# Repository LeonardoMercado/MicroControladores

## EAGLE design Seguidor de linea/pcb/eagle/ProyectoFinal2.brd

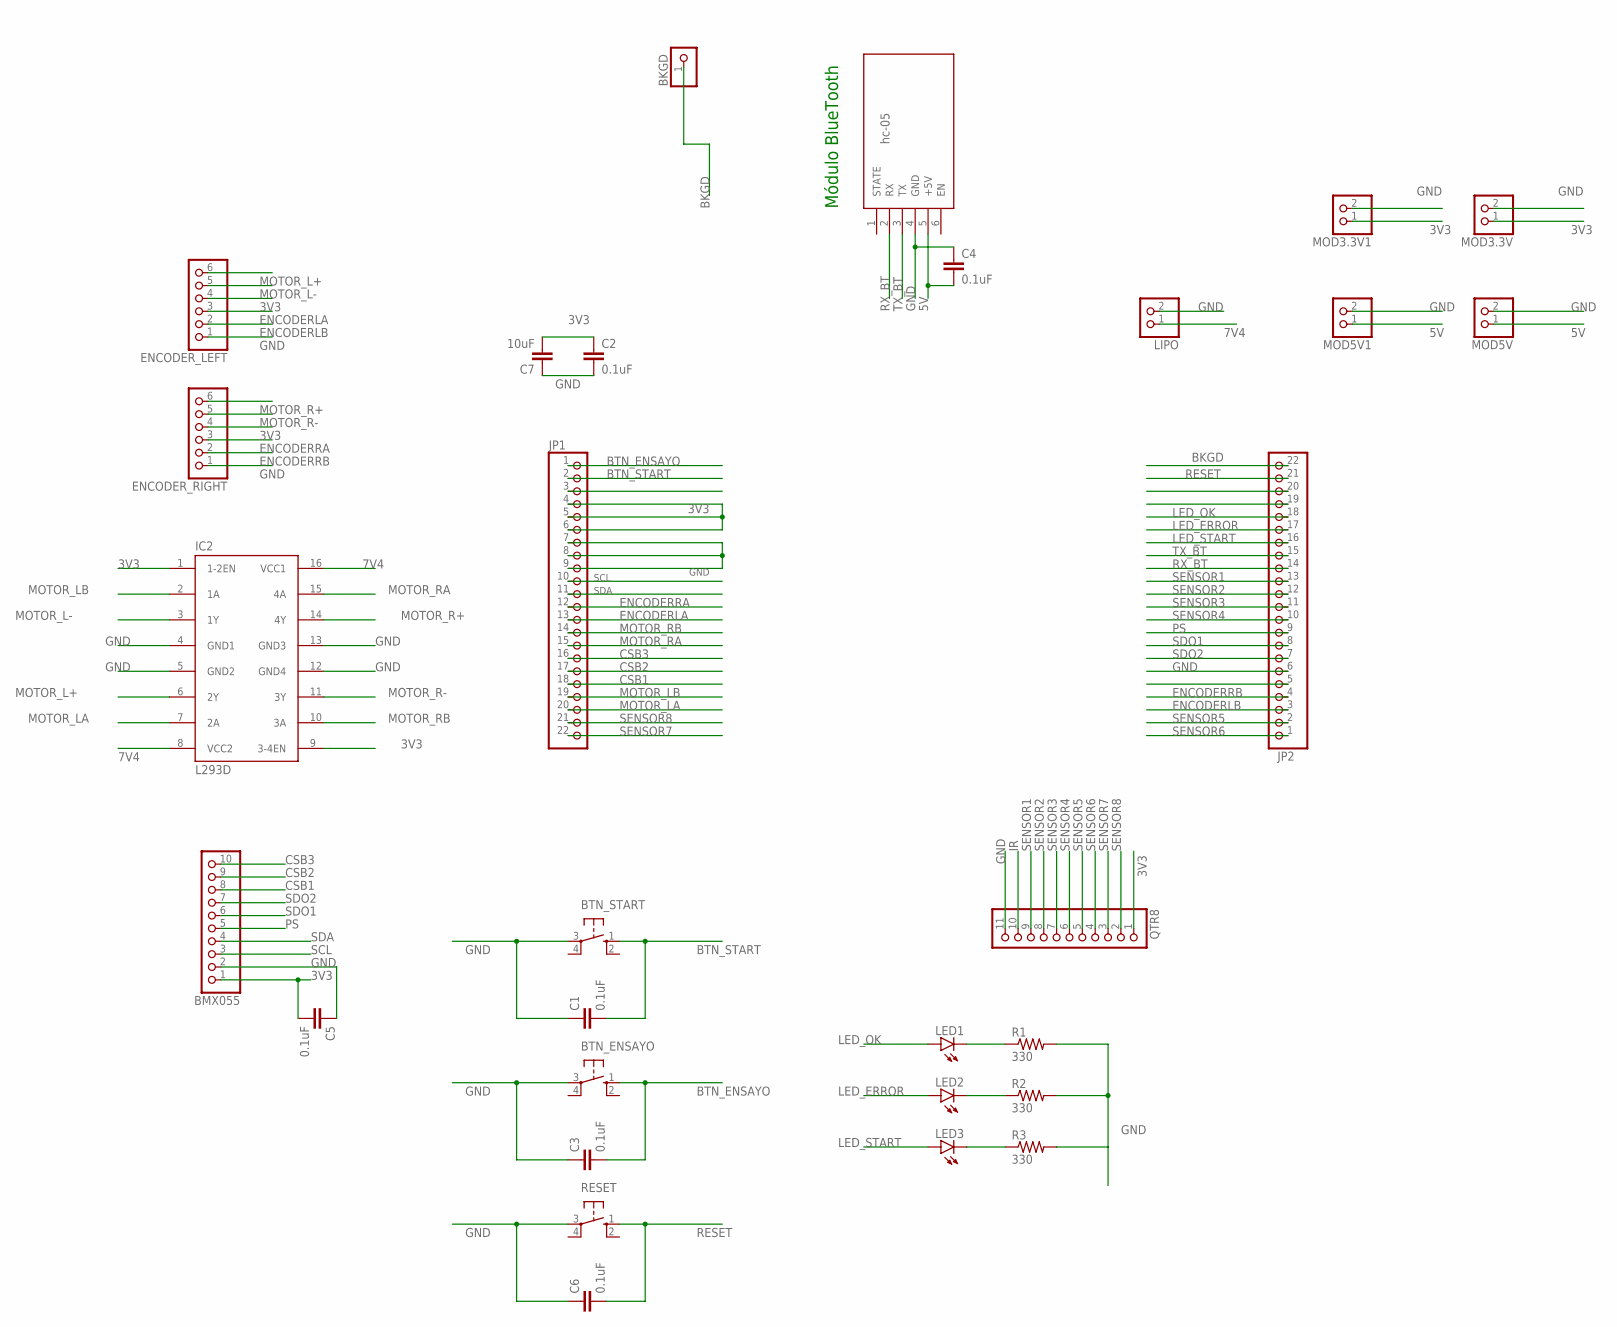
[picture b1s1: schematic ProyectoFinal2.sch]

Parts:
BKGD: PINHD-1X1; 1X01
BLUETOOTH: hc-05; WIRELESS-BLUETOOTH-HC-05
BMX055: PINHD-1X10; 1X10
BTN_ENSAYO: 10-XX; B3F-10XX
BTN_START: 10-XX; B3F-10XX
C1, C2, C3, C4, C5, C6: 0.1uF; C0805K
C7: 10uF; C1206K
ENCODER_LEFT: PINHD-1X6; 1X06
ENCODER_RIGHT: PINHD-1X6; 1X06
IC2: L293D; DIL16
JP1, JP2: PINHD-1X22; 1X22
LED1, LED2, LED3: LED5MM
LIPO: PINHD-1X2; 1X02
MOD3.3V, MOD3.3V1, MOD5V, MOD5V1: PINHD-1X2; 1X02
QTR8: PINHD-1X11; 1X11
R1, R2, R3: 330; R0805
RESET: 10-XX; B3F-10XX

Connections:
3V3: BMX055.1, C2.1, C5.2, C7.2, ENCODER_LEFT.4, ENCODER_RIGHT.4, IC2.1 (1-2EN), IC2.9 (3-4EN), JP1.4, JP1.5, JP1.6, MOD3.3V.1, MOD3.3V1.1, QTR8.1
5V: BLUETOOTH.5 (+5V), C4.2, MOD5V.1, MOD5V1.1
7V4: IC2.8 (VCC2), IC2.16 (VCC1), LIPO.1
BKGD: BKGD.1, JP2.22
BTN_ENSAYO: BTN_ENSAYO.1 (S), C3.2, JP1.1
BTN_START: BTN_START.1 (S), C1.2, JP1.2
CSB1: BMX055.8, JP1.18
CSB2: BMX055.9, JP1.17
CSB3: BMX055.10, JP1.16
ENCODERLA: ENCODER_LEFT.3, JP1.13
ENCODERLB: ENCODER_LEFT.2, JP2.3
ENCODERRA: ENCODER_RIGHT.3, JP1.12
ENCODERRB: ENCODER_RIGHT.2, JP2.4
GND: BLUETOOTH.4 (GND), BMX055.2, BTN_ENSAYO.3, BTN_START.3, C1.1, C2.2, C3.1, C4.1, C5.1, C6.1, C7.1, ENCODER_LEFT.1, ENCODER_RIGHT.1, IC2.4 (GND1), IC2.5 (GND2), IC2.12 (GND4), IC2.13 (GND3), JP1.7, JP1.8, JP1.9, JP2.6, LIPO.2, MOD3.3V.2, MOD3.3V1.2, MOD5V.2, MOD5V1.2, QTR8.11, R1.2, R2.2, R3.2, RESET.3
IR: QTR8.10
LED_ERROR: JP2.17, LED2.A
LED_OK: JP2.18, LED1.A
LED_START: JP2.16, LED3.A
MOTOR_L+: ENCODER_LEFT.6, IC2.6 (2Y)
MOTOR_L-: ENCODER_LEFT.5, IC2.3 (1Y)
MOTOR_LA: IC2.7 (2A), JP1.20
MOTOR_LB: IC2.2 (1A), JP1.19
MOTOR_R+: ENCODER_RIGHT.6, IC2.14 (4Y)
MOTOR_R-: ENCODER_RIGHT.5, IC2.11 (3Y)
MOTOR_RA: IC2.15 (4A), JP1.15
MOTOR_RB: IC2.10 (3A), JP1.14
unnamed: LED1.K (C), R1.1
unnamed: LED2.K (C), R2.1
unnamed: LED3.K (C), R3.1
PS: BMX055.5, JP2.9
RESET: C6.2, JP2.21, RESET.1 (S)
RX_BT: BLUETOOTH.2 (RX), JP2.14
SCL: BMX055.3, JP1.10
SDA: BMX055.4, JP1.11
SDO1: BMX055.6, JP2.8
SDO2: BMX055.7, JP2.7
SENSOR1: JP2.13, QTR8.9
SENSOR2: JP2.12, QTR8.8
SENSOR3: JP2.11, QTR8.7
SENSOR4: JP2.10, QTR8.6
SENSOR5: JP2.2, QTR8.5
SENSOR6: JP2.1, QTR8.4
SENSOR7: JP1.22, QTR8.3
SENSOR8: JP1.21, QTR8.2
TX_BT: BLUETOOTH.3 (TX), JP2.15

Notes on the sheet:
Módulo BlueTooth

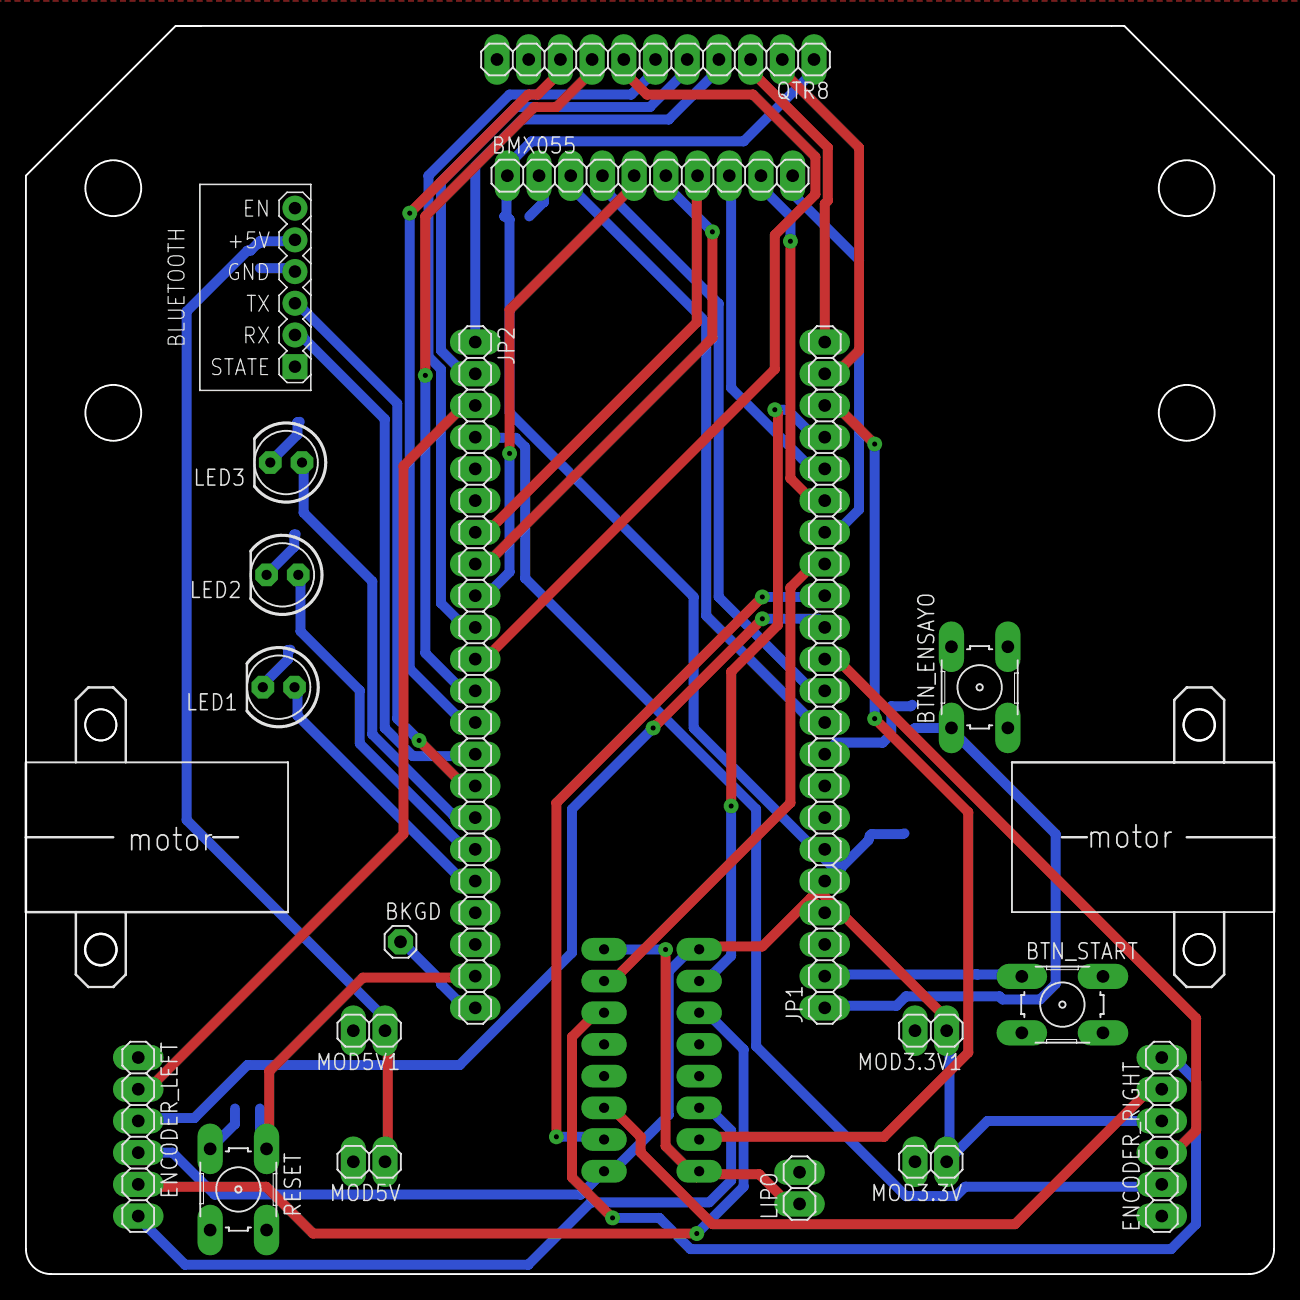
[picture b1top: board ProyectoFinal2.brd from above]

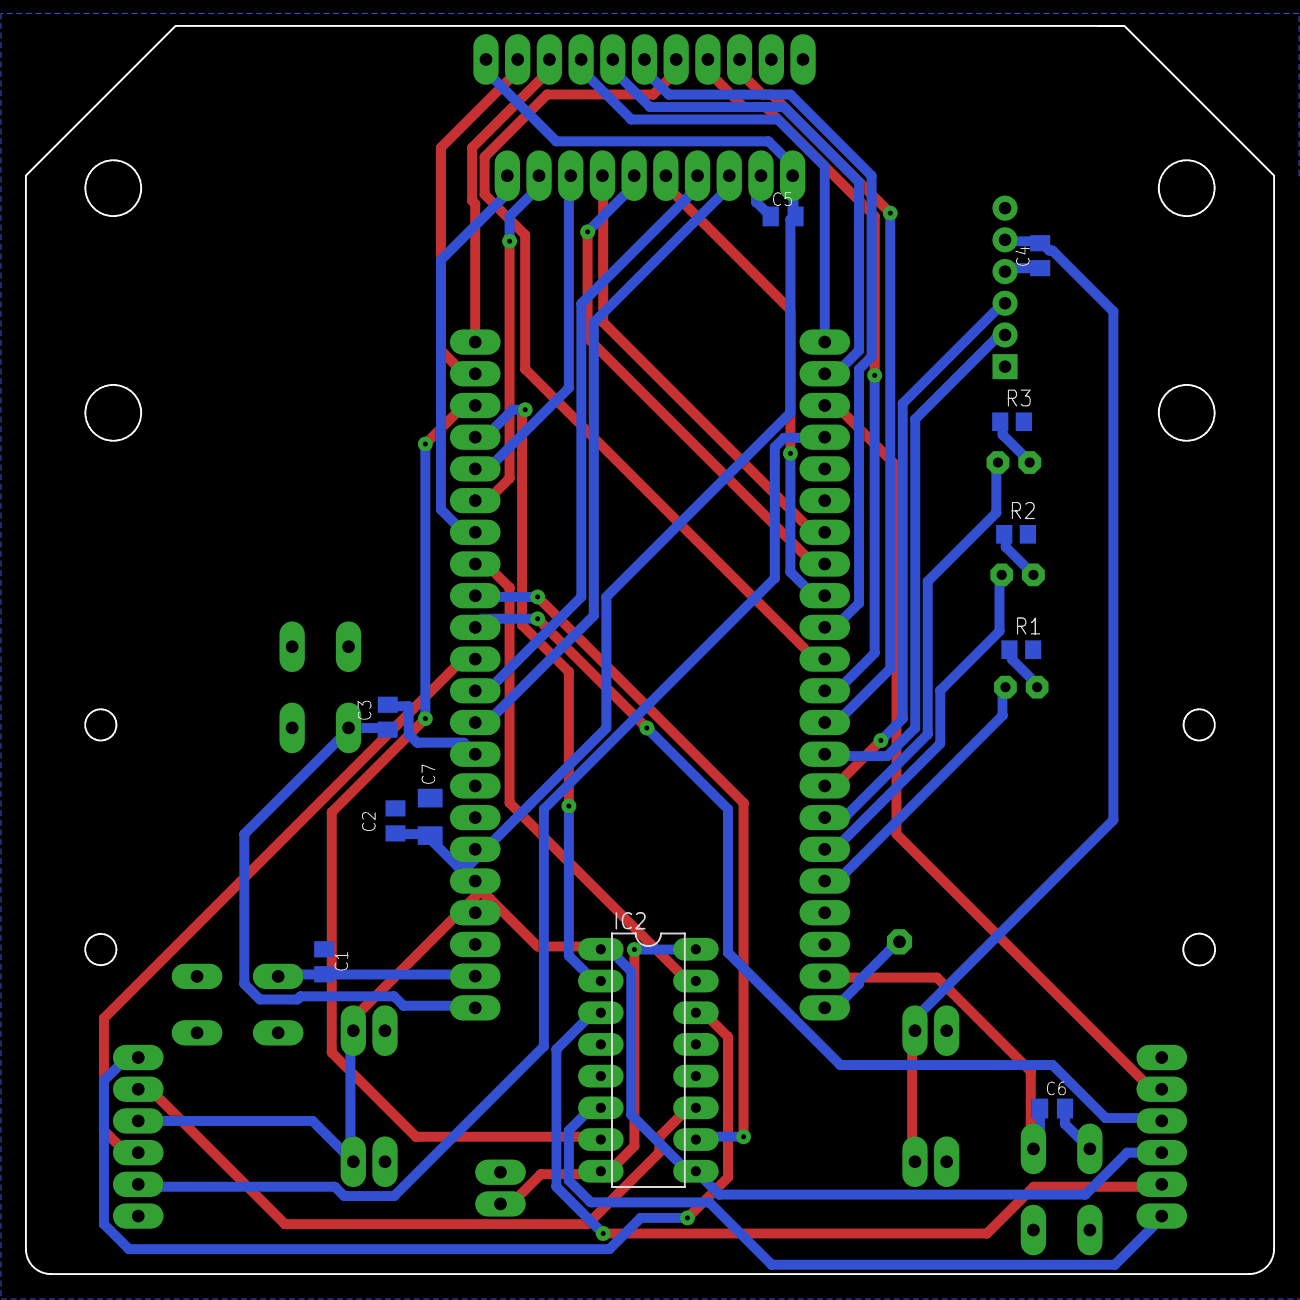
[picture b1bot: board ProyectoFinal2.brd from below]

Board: 2 copper layers, 100.0 x 100.0 mm, 30 parts (11 on the bottom side), 44 nets.

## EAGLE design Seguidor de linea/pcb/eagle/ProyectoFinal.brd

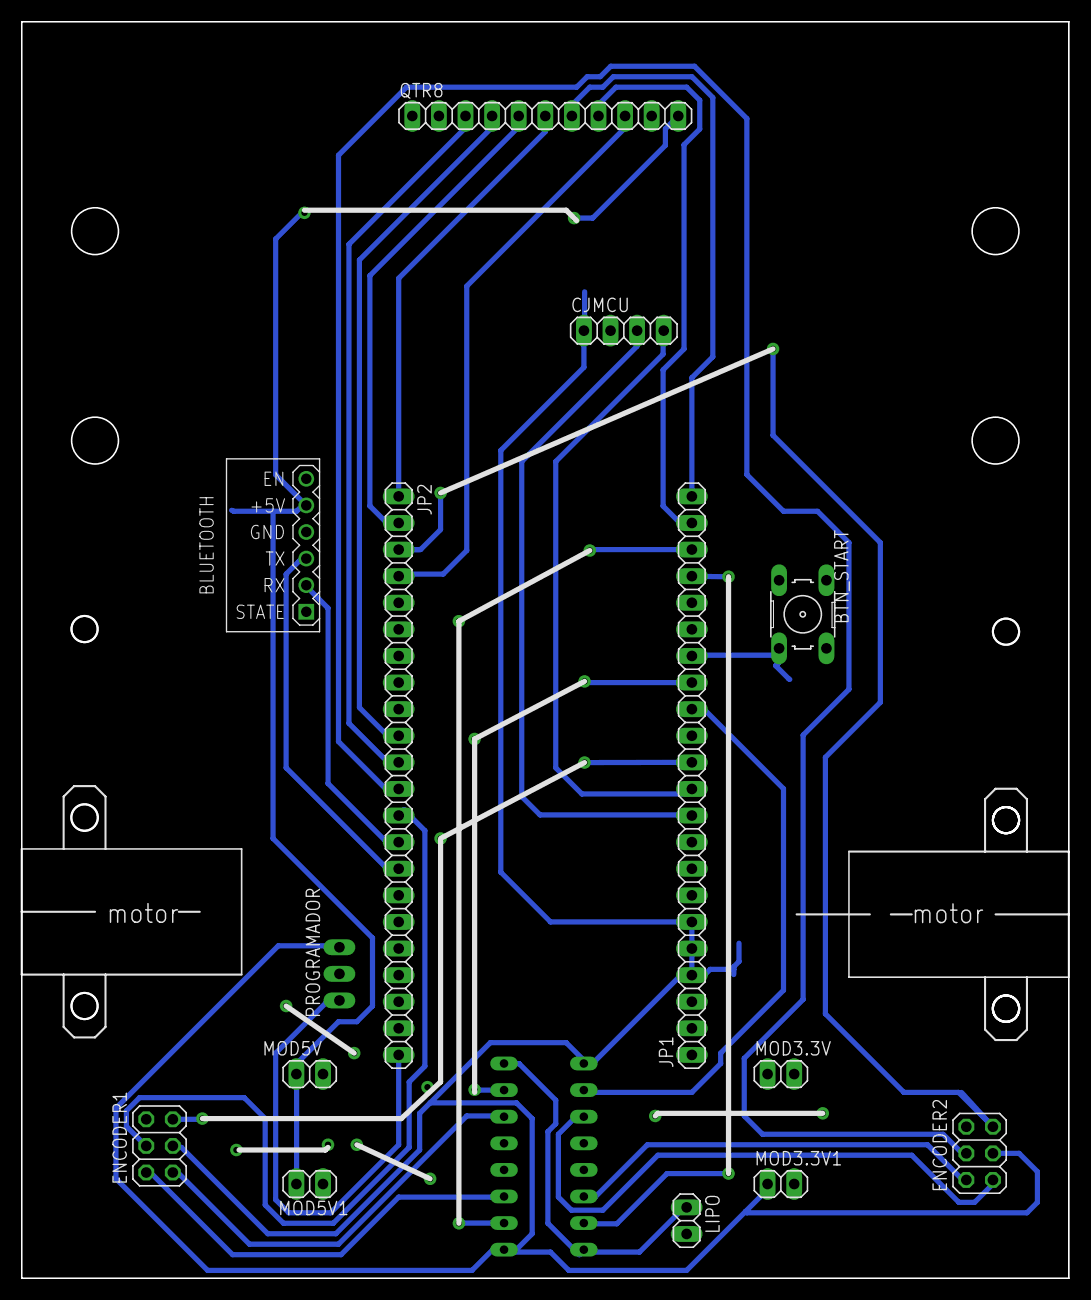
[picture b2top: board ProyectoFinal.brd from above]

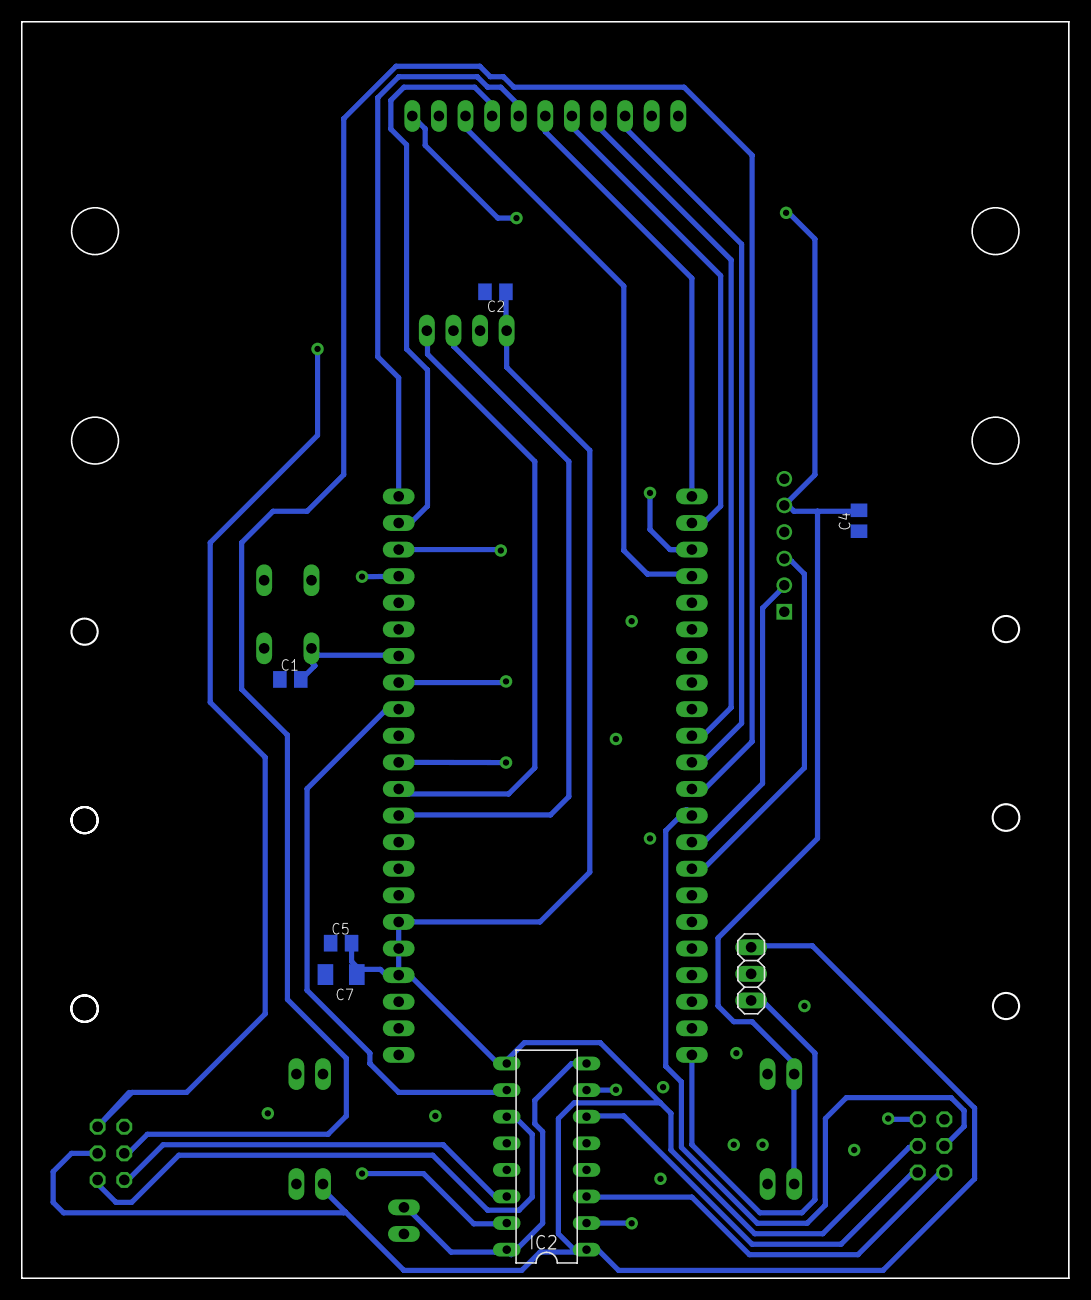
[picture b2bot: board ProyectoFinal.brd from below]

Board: 2 copper layers, 100.0 x 120.0 mm, 20 parts (7 on the bottom side), 29 nets.

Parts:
BLUETOOTH: hc-05; WIRELESS-BLUETOOTH-HC-05
BTN_START: B3F-10XX
C1, C2, C4, C5: 0.1uF; C0805K
C7: 10uF; C1206K
CJMCU: 1X04
ENCODER1, ENCODER2: 2X03
IC2: L293D; DIL16
JP1, JP2: 1X22
LIPO: 1X02
MOD3.3V, MOD3.3V1, MOD5V, MOD5V1: 1X02
PROGRAMADOR: 1X03
QTR8: 1X11

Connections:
3V3: C2.1, C5.2, C7.2, CJMCU.1, ENCODER1.3, ENCODER2.3, IC2.1, IC2.9, JP1.4, JP1.5, JP1.6, MOD3.3V1.1, PROGRAMADOR.3
5V: BLUETOOTH.5, C4.2, MOD5V.1, MOD5V1.1
7V4: IC2.8, IC2.16, LIPO.1
ADC2: JP2.11, QTR8.3
ADC3: JP2.10, QTR8.4
ADC4: JP2.2, QTR8.5
ADC5: JP2.1, QTR8.6
ADC6: JP1.22, QTR8.7
ADC7: JP1.21, QTR8.8
ADC8: JP2.4, QTR8.9
BKGD: JP2.22, PROGRAMADOR.1
BTN_START: BTN_START.1, C1.2, JP1.16
ENCODER1_1: ENCODER1.4, JP2.13
ENCODER1_2: ENCODER1.5, JP1.12
ENCODER2_1: ENCODER2.4, JP2.12
ENCODER2_2: ENCODER2.5, JP2.3
GND: BLUETOOTH.4, BTN_START.3, C1.1, C2.2, C4.1, C5.1, C7.1, CJMCU.2, ENCODER1.6, ENCODER2.6, IC2.4, IC2.5, IC2.12, IC2.13, JP1.7, JP1.8, JP1.9, JP2.6, LIPO.2, MOD3.3V.2, MOD3.3V1.2, MOD5V.2, MOD5V1.2, PROGRAMADOR.2, QTR8.1
MOTOR1_IN1: IC2.2, JP1.20
MOTOR1_IN2: IC2.7, JP1.15
MOTOR1_OUT1: ENCODER1.1, IC2.6
MOTOR1_OUT2: ENCODER1.2, IC2.3
MOTOR2_IN1: IC2.15, JP1.19
MOTOR2_IN2: IC2.10, JP1.14
MOTOR2_OUT1: ENCODER2.1, IC2.11
MOTOR2_OUT2: ENCODER2.2, IC2.14
RX_BT: BLUETOOTH.2, JP2.14
SCL: CJMCU.3, JP1.10
SDA: CJMCU.4, JP1.11
TX_BT: BLUETOOTH.3, JP2.15

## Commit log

2019-04-13 v1.0
    Se implementa el código enviado al correo
2019-04-13 v1.1
    Se modifico el puerto de entrada del push button y el puerto de salida del led
2019-04-16 V1.0
    Se implementa el código enviado, se analiza linea a linea y se comenta su acción
2019-04-23 vs 1.0
    Se implementa el código para encender 1 led y se modifican los puertos de entrada y de salida.
2019-04-23 v1.1
    Se realizan cambios en las etiquetas a implementar.
2019-04-24 Create freqLedRGB.asm
    Encendido led RGB cada 2.5s
2019-04-24 v1.2
    Se implementa el antirebote por SW y las especificaciones de los OpCode y los modos de direcionamiento
2019-05-03 v1.3
    Se implementa el Debugger de la etiqueta antirrebote.
2019-05-08 Ajuste leds y RTI lab4
2019-05-08 Código de retardos funcionando
2019-05-08 Direccionamiento indexado sin offset
2019-05-14 Código toggle_led T=4s
2019-05-14 Incluye vector interrupción MITM
2019-05-14 Código comentado
2019-05-21 Revert "V2"
    This reverts commit e91b2cf7e1e8bfc91f57d2a8d6e4e909c6e53531, reversing
    changes made to 079b767442dc883627aac7999d236b1ab7ce7748.
2019-05-21 Revert "Revert "V2""
    This reverts commit bc979bf9f36cf7630d5f124ff7b2e6652c294545.
2019-05-27 ajuste interrupción RTC
2019-05-28 v1.0
    Se carga el avanze del Laboratorio 7
2019-05-29 v1.1
    Se realizan mejoras y rotulados necesarios.
2019-05-29 V 1.1
2019-05-30 V.1.0
    Código ej Sebastian baud rate 19200 sin paridad FUNCIONANDO
2019-05-31 v1.0
    blalgl
2019-05-31 V1.0
2019-05-31 Reciclado del Lab6
    Reciclado, hay que hacerle algunas modificaciones
2019-05-31 Reciclado Lab6
    Actualizado: Display muestra un dato numerico, enciende el led RGB con los 3 botones, ahora los botones start/stop funcionan ambos para detener el cronometro y hacerlo andar de manera ascendente/desc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
2019-05-31 Add files via upload
    Lab7 - Falta enviar/recibir datos
2019-05-31 V 2.0
2019-06-12 v1.1
    Se completa la IHM para el laboratorio #8
2019-06-12 V1.1
2019-06-12 Create Lab8ADC.c
    Conversión de 12bits ADCClck=BusClck
    Se envían parte alta,baja y cambio de línea de manera consecutiva con retardo ente cada envío.
    Dudas*: revisar acknoledge ADC, y valores de ADCfreq máx y mín.
    Pendiente verificar funcionamiento.
2019-06-12 v1.0
    Configuracion de pines, falta KBI
2019-06-13 Version 1.1
    Prueba del ADC (funcionando) y configuraciones iniciales, Enviar datos bloquea el micro
2019-06-13 V1.2
2019-06-14 Interfaz 12 bits
2019-06-14 Interfaz funcionando 12 bits
2019-06-22 V 1.0
2019-06-22 Caracteres de verificación
    Se incluye envío y recepción de datos para sincronizar lacomunicación. El divisor de Baud Rate sube a 16.
2019-06-25 Base Interfaz Laboratorio 8
2019-06-26 v1.0
    Segunda versión de la PCB
2019-06-26 V1.0
    INFORME CORRESPONDIENTE AL LAB#9
2019-06-26 V1.0
    Primera version de la GUI del lab#9
2019-06-27 TMP y PWM funcionando
2019-07-13 Create InterfazSeguidor.pde
    Interfaz incluye ADC y Velocidad Angular. Pendiente Velocidad lineal y giroscopio*
2019-07-14 Sensores+Encoder+PWM
    Interfaz gráfica y código C:Envío de datos de los sensores, posición y error de posiión. Envío de pwm a los motores, lectura de los encoders y envío de velocidad angular de los motores.
2019-07-14 Lab9
2019-07-15 v1.0
    Carpeta para el control de velocidad
2019-07-15 Control de velocidad
    Se implementa control de velocidad para cada uno de los motores

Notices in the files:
parts and their libraries:
diy-modules: Released under the Creative Commons Attribution 4.0 International License: http://creativecommons.org/licenses/by/4.0
